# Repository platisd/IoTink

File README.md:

# IoTink
Your portable & connected, e-paper dashboard

## What?
**IoT + E-Ink = IoTink**

IoTink is a portable dashboard using an e-paper display and is connected to the
Internet. It is currently utilized to fetch public transport departures and
weather predictions from a
[web service](https://github.com/platisd/vasttrafik-google-assistant) but could
be easily repurposed to accomodate different use cases.

## Why?
IoTink is ideal for times when you need to fetch information via WiFi and display
them on a screen, but it is not feasible to install power cables.

As long as you do not need real-time or frequent updates, IoTink should be
able to remain powered up on 4 AA batteries for a while.

## How?
The concept is rather straightforward, with an ESP8266 microcontroller fetching
data over WiFi and displaying them on the e-paper screen. Then it goes to
deep sleep until it is time to ome back online and fetch updated data.

On a hardware level, things are kept simple, with a minimum ESP8266 circuit that
enables us to program the chip when necessary via UART. 2+2 AA batteries are
supplying just enough voltage for the microcontroller to operate seamlessly.

### Components
* [IoTink PCB rev.0](https://www.pcbway.com/project/shareproject/IoTink__Your_portable_e_paper_dashboard.html)
* [4.2" e-paper module by Waveshare](https://www.waveshare.com/wiki/4.2inch_e-Paper_Module)
* ESP12F
* [4x AA battery holders](https://www.electrokit.com/produkt/batterihallare-1xaa-pcb/) [(Dimensions)](https://i.imgur.com/DCF7JLv.jpg)
* 4x 10KOhm resistors
* 100nF capacitor
* On/Off tactile switch
* 2x 3-pin male headers
* 2x Jumpers
* 6-pin female header
* 8-pin female header

### Software dependencies
* [GxEPD](https://github.com/ZinggJM/GxEPD/) library for controlling the e-paper display
* [Adafruit GFX](https://github.com/adafruit/Adafruit-GFX-Library) library for the graphics
* [ArduinoJson](https://github.com/bblanchon/ArduinoJson) library for parsing JSON

## Media
* [Background story](https://platis.solutions/blog/2019/02/18/iotink-your-portable-e-paper-dashboard/)
* [Demo video](https://youtu.be/FovcpUYtC_o)

## License
The IoTink project is released under a dual licensing scheme, because we
are obligated to use a copyleft license for the software.

### Software
**GPLv3** - The license had to be selected due to depending on GPL'd software,
i.e. the [GxEPD](https://github.com/ZinggJM/GxEPD/) library. Pull requests that
will enable this project adopt a more permissive license are more than welcome.

### Hardware
**CC-BY 4.0**

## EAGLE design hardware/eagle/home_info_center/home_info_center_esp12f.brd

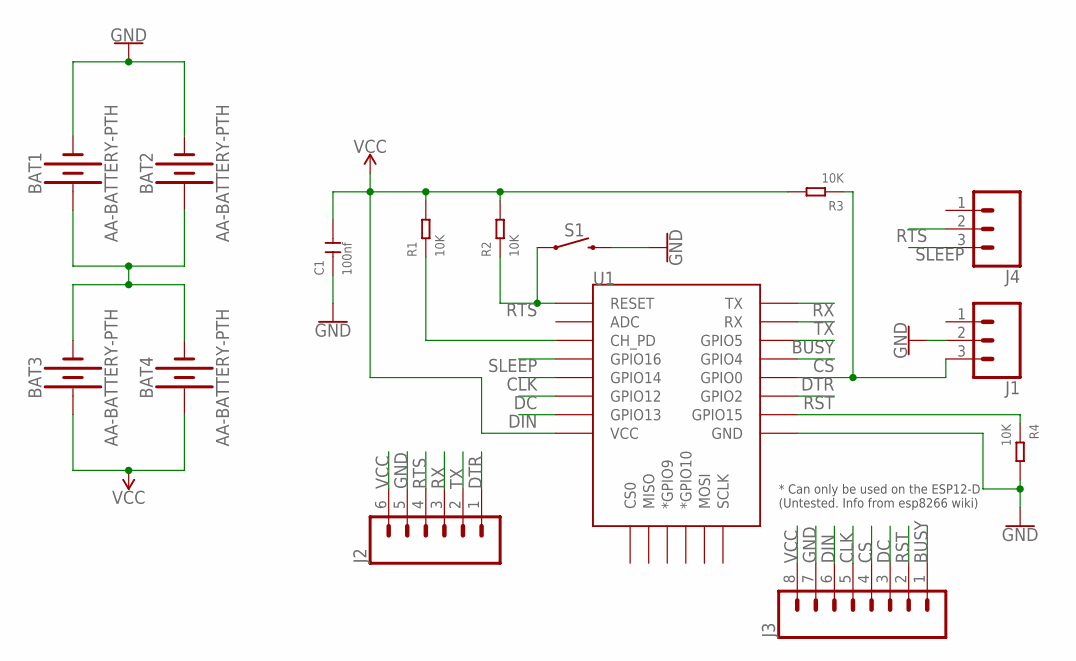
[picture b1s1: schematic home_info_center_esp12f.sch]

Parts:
BAT1, BAT2, BAT3, BAT4: AA-BATTERY-PTH; AA-PCB-BATTERY
C1: 100nf; CERAMIC-2.54
J1, J4: CONN_03; 1X03
J2: CONN_06LOCK; 1X06_LOCK
J3: CONN_08LOCK; 1X08_LOCK
R1, R2, R3, R4: 10K; PR-D2.3XL6.5MM
S1: MOMENTARY-SWITCH-SPST-PTH-6.0MM-KIT; TACTILE_SWITCH_PTH_6.0MM_KIT
U1: ESP12ESMD; ESP12E-SMD

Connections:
BUSY: J3.1, U1.GPIO5
CLK: J3.5, U1.GPIO14
CS: J3.4, U1.GPIO4
DC: J3.3, U1.GPIO12
DIN: J3.6, U1.GPIO13
DTR: J1.3, J2.1, R3.1, U1.GPIO0
GND: BAT1.NEG (-), BAT2.NEG (-), C1.1, J1.2, J2.5, J3.7, R4.2, S1.3 (2), U1.GND
unnamed: R1.1, U1.CH_PD
unnamed: R4.1, U1.GPIO15
unnamed: BAT1.POS (+), BAT2.POS (+), BAT3.NEG (-), BAT4.NEG (-)
RST: J3.2, U1.GPIO2
RTS: J2.4, J4.2, R2.1, S1.1, U1.RESET
RX: J2.3, U1.TXD0 (TX)
SLEEP: J4.3, U1.GPIO16
TX: J2.2, U1.RXD0 (RX)
VCC: BAT3.POS (+), BAT4.POS (+), C1.2, J2.6, J3.8, R1.2, R2.2, R3.2, U1.VCC

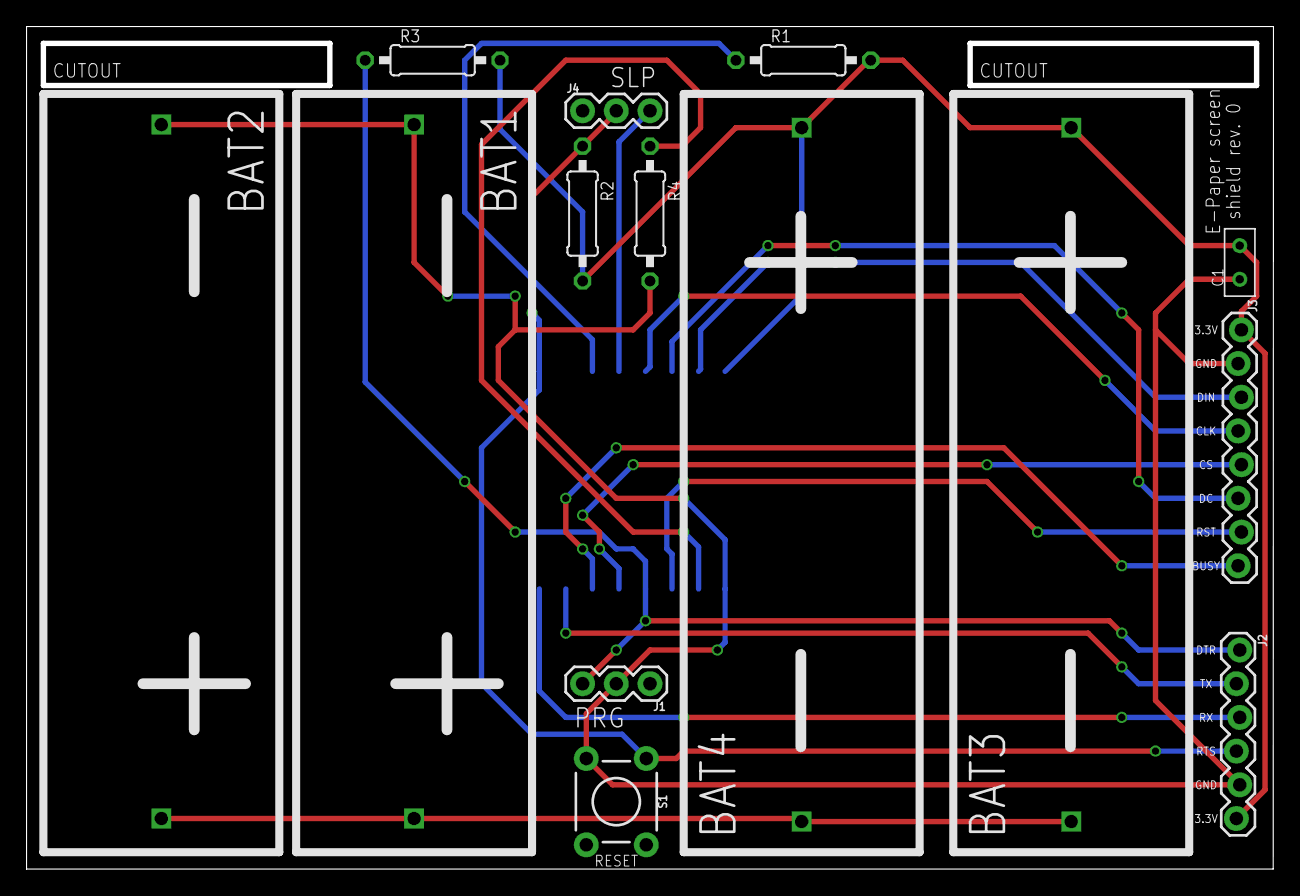
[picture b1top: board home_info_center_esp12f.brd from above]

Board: 2 copper layers, 93.6 x 63.1 mm, 15 parts (1 on the bottom side), 16 nets.

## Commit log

2019-02-17 Ignore vscode settings directory
2019-04-08 Add forgotten dependency to ArduinoJSON
2019-04-08 Decrease execution time
    * Remove serial print outs
    * Increase long sleep time during the night
    * Remove unused method
2019-04-08 Formatting fix
2019-04-08 Add rev.0 PCB design
    TODO for rev.1:
    * Move BAT4 to the right so to be evenly spaced
    * Add ON/OFF switch
    * Add MCP1700-3302E LDO
2019-04-08 Add project information
2019-04-08 Add IoTink Arduino sketch
2019-04-08 Sleep longer in the night
    In order to consume less power, sleep for about an hour
    during the night when no one is probably using the IoTink
2019-04-08 Add link to purchase from PCBWay
2020-06-26 Fix broken image link

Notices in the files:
parts and their libraries:
SparkFun-Connectors: Licensing: Creative Commons ShareAlike 4.0 International - https://creativecommons.org/licenses/by-sa/4.0
